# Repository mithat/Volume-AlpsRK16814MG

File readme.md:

Volume-AlpsRK16814MG
====================

_Because volume control is free and for the people.™_

Description
-----------
[KiCad 5.0](http://www.kicad.org) design files for a PCB that integrates an 
Alps RK16814MG motorized potentiometer with an H bridge to drive the motor
using logic-level signals.

### Inputs and outputs

| Name             | Function  |
|------------------|-----------|
| `VOL_UP`         | Logical input to rotate the potentiometer clockwise. |
| `VOL_DOWN`       | Logical input to rotate the potentiometer counter-clockwise. |
| `V_MOT`          | Power for motor drive. Nominally 6 VDC, but see comments below. |
| `+5VD`           | Power for logic circuits. 5 VDC. |
| `DGND`           | Ground for digital (logic) circuits. |
| `CHASSIS GROUND` | Ground for potentiometer case. Also labeled as C.G. on top side of PCB. |
| `A_TOP`          | Potentiometer A input |
| `A_WIPER`        | Potentiometer A output |
| `AB_COMMON`      | Potentiometer A and B's common (typically connects to signal ground) |
| `B_TOP`          | Potentiometer B input |
| `B_WIPER`        | Potentiometer A output |
| `C_TOP`          | Potentiometer C input |
| `C_WIPER`        | Potentiometer C output |
| `CD_COMMON`      | Potentiometer C and D's common (typically connects to signal ground) |
| `D_TOP`          | Potentiometer D input |
| `D_WIPER`        | Potentiometer D output |

### Power
There are two power inputs to the board, one for the 5 VDC logic (`+5VD`)
and the other to drive the potentiometer's motor (`V_MOT`). The board has a 
jumper (`J1`) that when installed will connect `V_MOT` to `+5VD`---making it
possible to operate the module from just one `+5VDC` power source, albeit with
a couple caveats.

First, owing to the voltage drop across the Darlington H-bridge, the optimum 
voltage for `V_MOT` is 6 VDC. When `V_MOT` is 5 VDC, the resulting voltage
delivered to the Alps RK16814MG's motor falls below Alps' specified minimum. 
However, the motor seems to have no problem operating at this lower than 
specified voltage. Second, the motor's maximum specified current consumption is 
150 mA. This is beyond the capacity of, for example, the on-board regulators
found on many Arduinos. Therefore, if you opt to jumper J1, you may have to use 
an external logic supply if you are using something like an Arduino for 
control.

### Grounding
The logic supply ground is completely isolated from other grounds. For the love 
of all  that is good, don't mix your logic and audio grounds. Connect the
logic and audio grounds at one point only and as close to the main power 
supplies as possible.

It is assumed the case of the potentiometer is grounded through the chassis. A
ground pin labeled `C.G.` is provided if this is not the case. This connection 
should not be used as a signal ground but rather only to provide a shielding 
connection for the potentiometer's case.

The potentiometer internally connects the "ground" sides of both elements of 
each gang. These are brought out as independent commons (`AB_COMMON` and 
`CD_COMMON`). Typically, `AB_COMMON` and `CD_COMMON` will be connected to 
signal ground.

### Use
While it's possible to use the **Volume-AlpsRK16814MG** PCB for applications 
other than volume control, we assume that you will be using it for volume 
control.

The Alps RK16814MG consists of two gangs of dual potentiometers. Refer to the
table above for the PCB's I/O corresponding to these.

For regular (non-differential) stereo use, you have the option of using both
elements of one gang (e.g., A and B) or one element from from each gang (e.g., 
A and C).

For differential stereo control, both elements on both gangs will be required.

To rotate the potentiometer CW (i.e., up), apply a logical 1 to `VOL_UP` and a
logical 0 to `VOL_DOWN`. To rotate the potentiometer CCW (i.e., down), apply a 
logical 1 to `VOL_DOWN` and a logical 0 to `VOL_UP`. No harm will come if a 
logical 1 is applied to both `VOL_UP` and `VOL_DOWN` simultaneously.

License
-------
CERN Open Hardware License v1.2 

Copyright
---------
Copyright (C) 2015 Mithat Konar.

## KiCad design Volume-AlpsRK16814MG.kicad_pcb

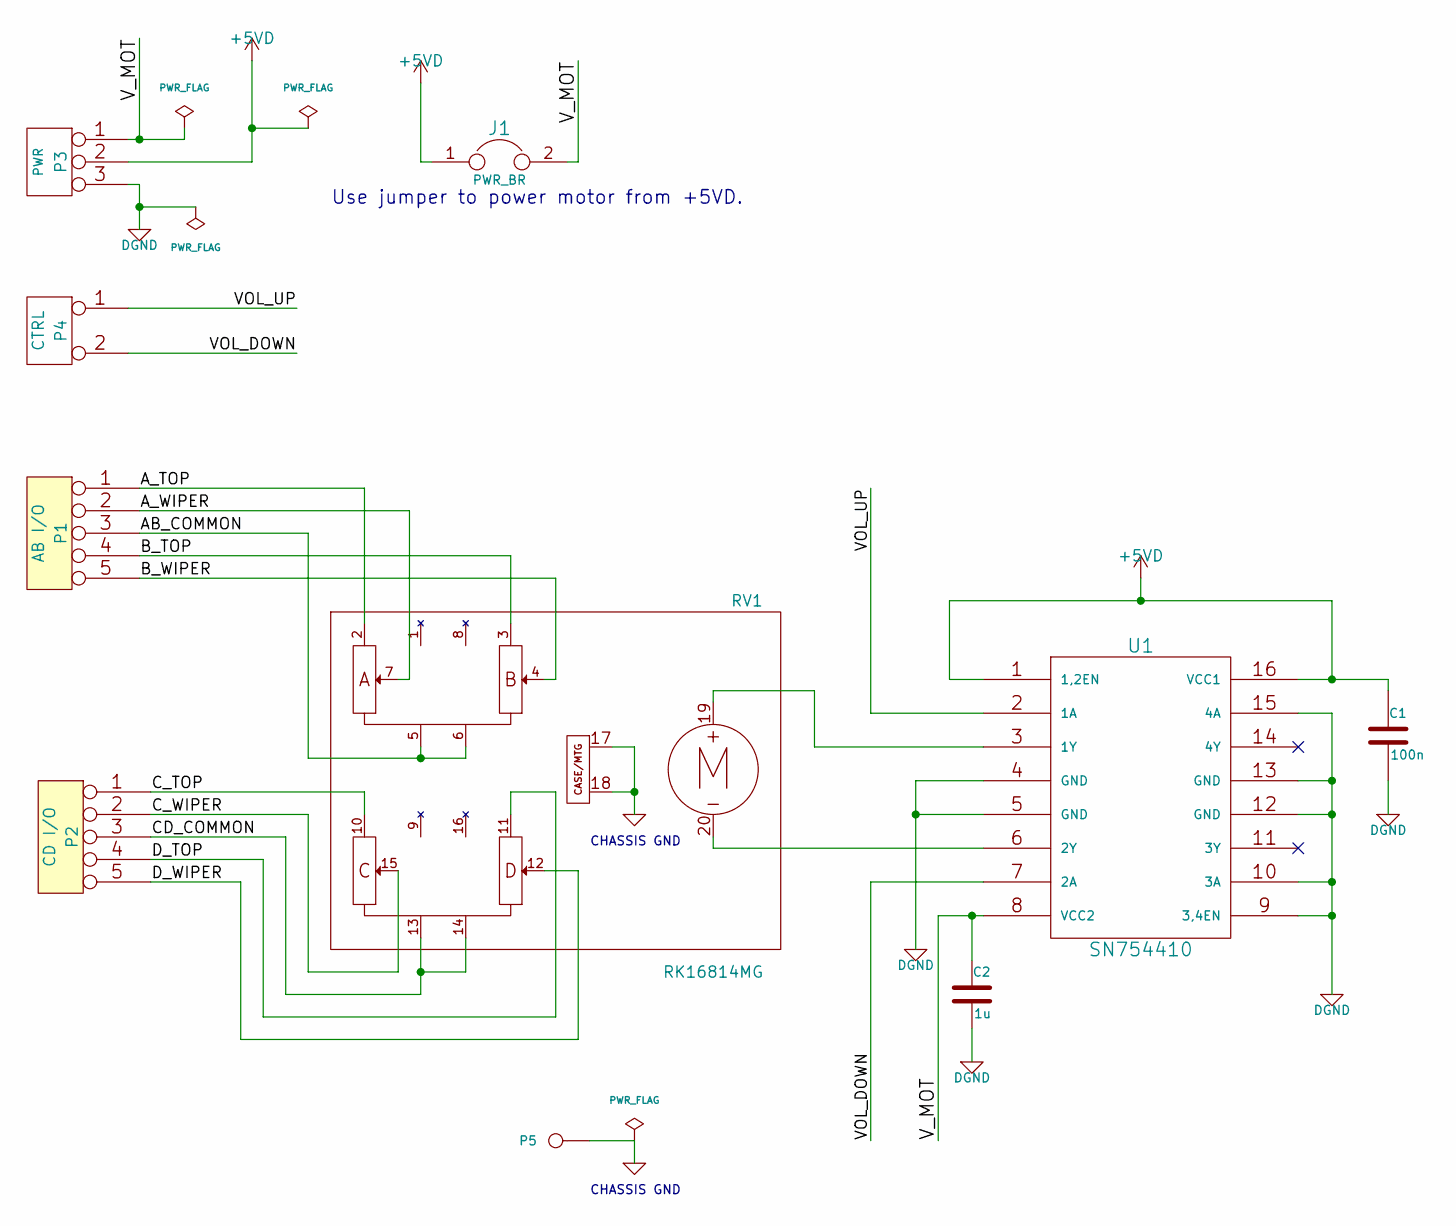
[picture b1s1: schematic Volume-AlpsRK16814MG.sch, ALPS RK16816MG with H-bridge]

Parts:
C1: 100n; C_4.0_2.5_2.5_0.5
C2: 1u; C_4.0_2.5_2.5_0.5
J1: PWR_BR; SIL-2
P1: AB I/O; TE_282834-5
P2: CD I/O; TE_282834-5
P3: PWR; TE_282834-3
P4: CTRL; TE_282834-2
P5: GND; AVA-20ga
RV1: RK16814MG; ALPS_RK16814MG
U1: SN754410; DIP-16_AriesC84_e

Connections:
+5VD: C1.1, J1.1, P3.2 (PM), U1.1 (1,2EN), U1.16 (VCC1)
/AB_COMMON: P1.3, RV1.5 (ABcommon), RV1.6 (ABcommon)
/A_TOP: P1.1, RV1.2 (A1)
/A_WIPER: P1.2, RV1.7 (A2)
/B_TOP: P1.4, RV1.3 (B1)
/B_WIPER: P1.5, RV1.4 (B2)
/CD_COMMON: P2.3, RV1.13 (CDcommon), RV1.14 (CDcommon)
/C_TOP: P2.1, RV1.10 (C1)
/C_WIPER: P2.2, RV1.15 (C2)
/D_TOP: P2.4, RV1.11 (D1)
/D_WIPER: P2.5, RV1.12 (D2)
/VOL_DOWN: P4.2 (PM), U1.7 (2A)
/VOL_UP: P4.1, U1.2 (1A)
/V_MOT: C2.1, J1.2, P3.1, U1.8 (VCC2)
DGND: C1.2, C2.2, P3.3, U1.4 (GND), U1.5 (GND), U1.9 (3,4EN), U1.10 (3A), U1.12 (GND), U1.13 (GND), U1.15 (4A)
GND: P5.1, RV1.17 (Case), RV1.18 (Case)
unnamed: RV1.19 (Vmotor+), U1.3 (1Y)
unnamed: RV1.20 (Vmotor-), U1.6 (2Y)

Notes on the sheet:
CHASSIS GND
Use jumper to power motor from +5VD.

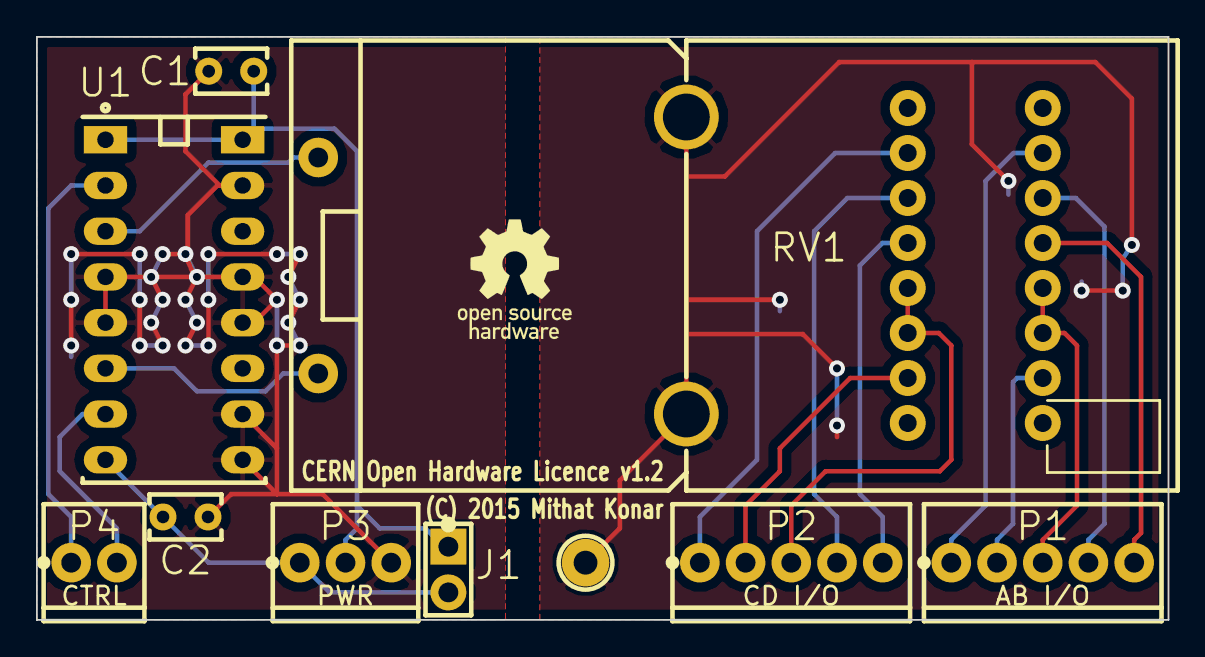
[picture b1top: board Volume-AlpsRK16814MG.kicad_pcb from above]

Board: 2 copper layers, 62.9 x 32.4 mm, 12 parts (1 on the bottom side), 18 nets.

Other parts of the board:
LOGO1: REF; oshw-logo-250mil-FSilk
LOGO2: REF; oshw-logo-notext-100mil-FSilk

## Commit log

2015-03-21 Initial commit. Pre-route.
2015-03-21 Routed.
2015-03-21 Flooded.
2015-03-21 Added bypass C to VCC2.
2015-03-22 Added cap to VCC2. Stitched SN754410 GND for heat.
2015-03-22 The terse readme.
2015-03-22 Added (C) and other additional labels silkscreen.
2015-03-23 Schematic presentation tweak.
2015-03-27 Silkscreen optimizations. Added license to silkscreen.
2015-04-03 Silk tweaks.
2015-04-03 Schematic changes for independent motor drive voltage.
2015-04-04 Added jumper to connect motor and digital supplies to schematic; PCB updated.
2015-04-04 .gitignore ignores top-level zip, png, and svg files. Added docs dir.
2015-04-05 Major readme content.
2015-04-05 Added inputs/outputs section to readme and refined content.
2015-04-05 readme refinements.
2015-04-07 Added OSHW logo to sources.
2015-04-09 Changed labels on PCB and schematic so names are consistent. Readme tweak.
2019-05-13 Schematic updated to KiCad 5.
2019-05-14 Initial changes for converting PCB to KiCad 5.
2019-05-14 Silk changes.
2019-05-14 Update readme with tool obsolescence info.
2019-05-14 Update readme with KiCad version info.
2019-05-15 Moved footprints into local archive.
2019-05-16 Minor silkscreen adjustment.
2021-11-10 Update readme.md
    https://forum.kicad.info/t/warning-avoid-all-links-to-kicad-pcb-org-use-kicad-org/31521

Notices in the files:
Volume-AlpsRK16814MG.kicad_pcb:
CERN Open Hardware Licence v1.2
